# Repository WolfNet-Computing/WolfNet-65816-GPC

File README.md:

# WolfNet-65816-GPC
 WolfNet Computing 65816 based General Purpose Computer

Intended as an upgrade to the WolfNet-65C02-WBC, this computer is more general purpose in design and nature. Text-based USB-Serial control makes connecting to it easy. You don't even need a spare screen or keyboard. Plug it in to your computer, power it on and away you go.

Features:  
 - 65C816 Based design
 - USB Type-B Connnector, MCP2200 and SC28L91 for I/O (Think keyboard, mouse and screen but as a program on your PC, connecting to the device.)
 - ATF1508AS Based Reprogrammable Address Decoder and DMA Controller
 - ATX 20-Pin Power Connector
 - 65-SIB Serial Interface Bus
 - 40-Pin IDE Connector for PATA HDDs
 - 16 MiB Flash ROM
 - 16 MiB SRAM
 - Built-in JTAG-ISP Header for ATF1508AS

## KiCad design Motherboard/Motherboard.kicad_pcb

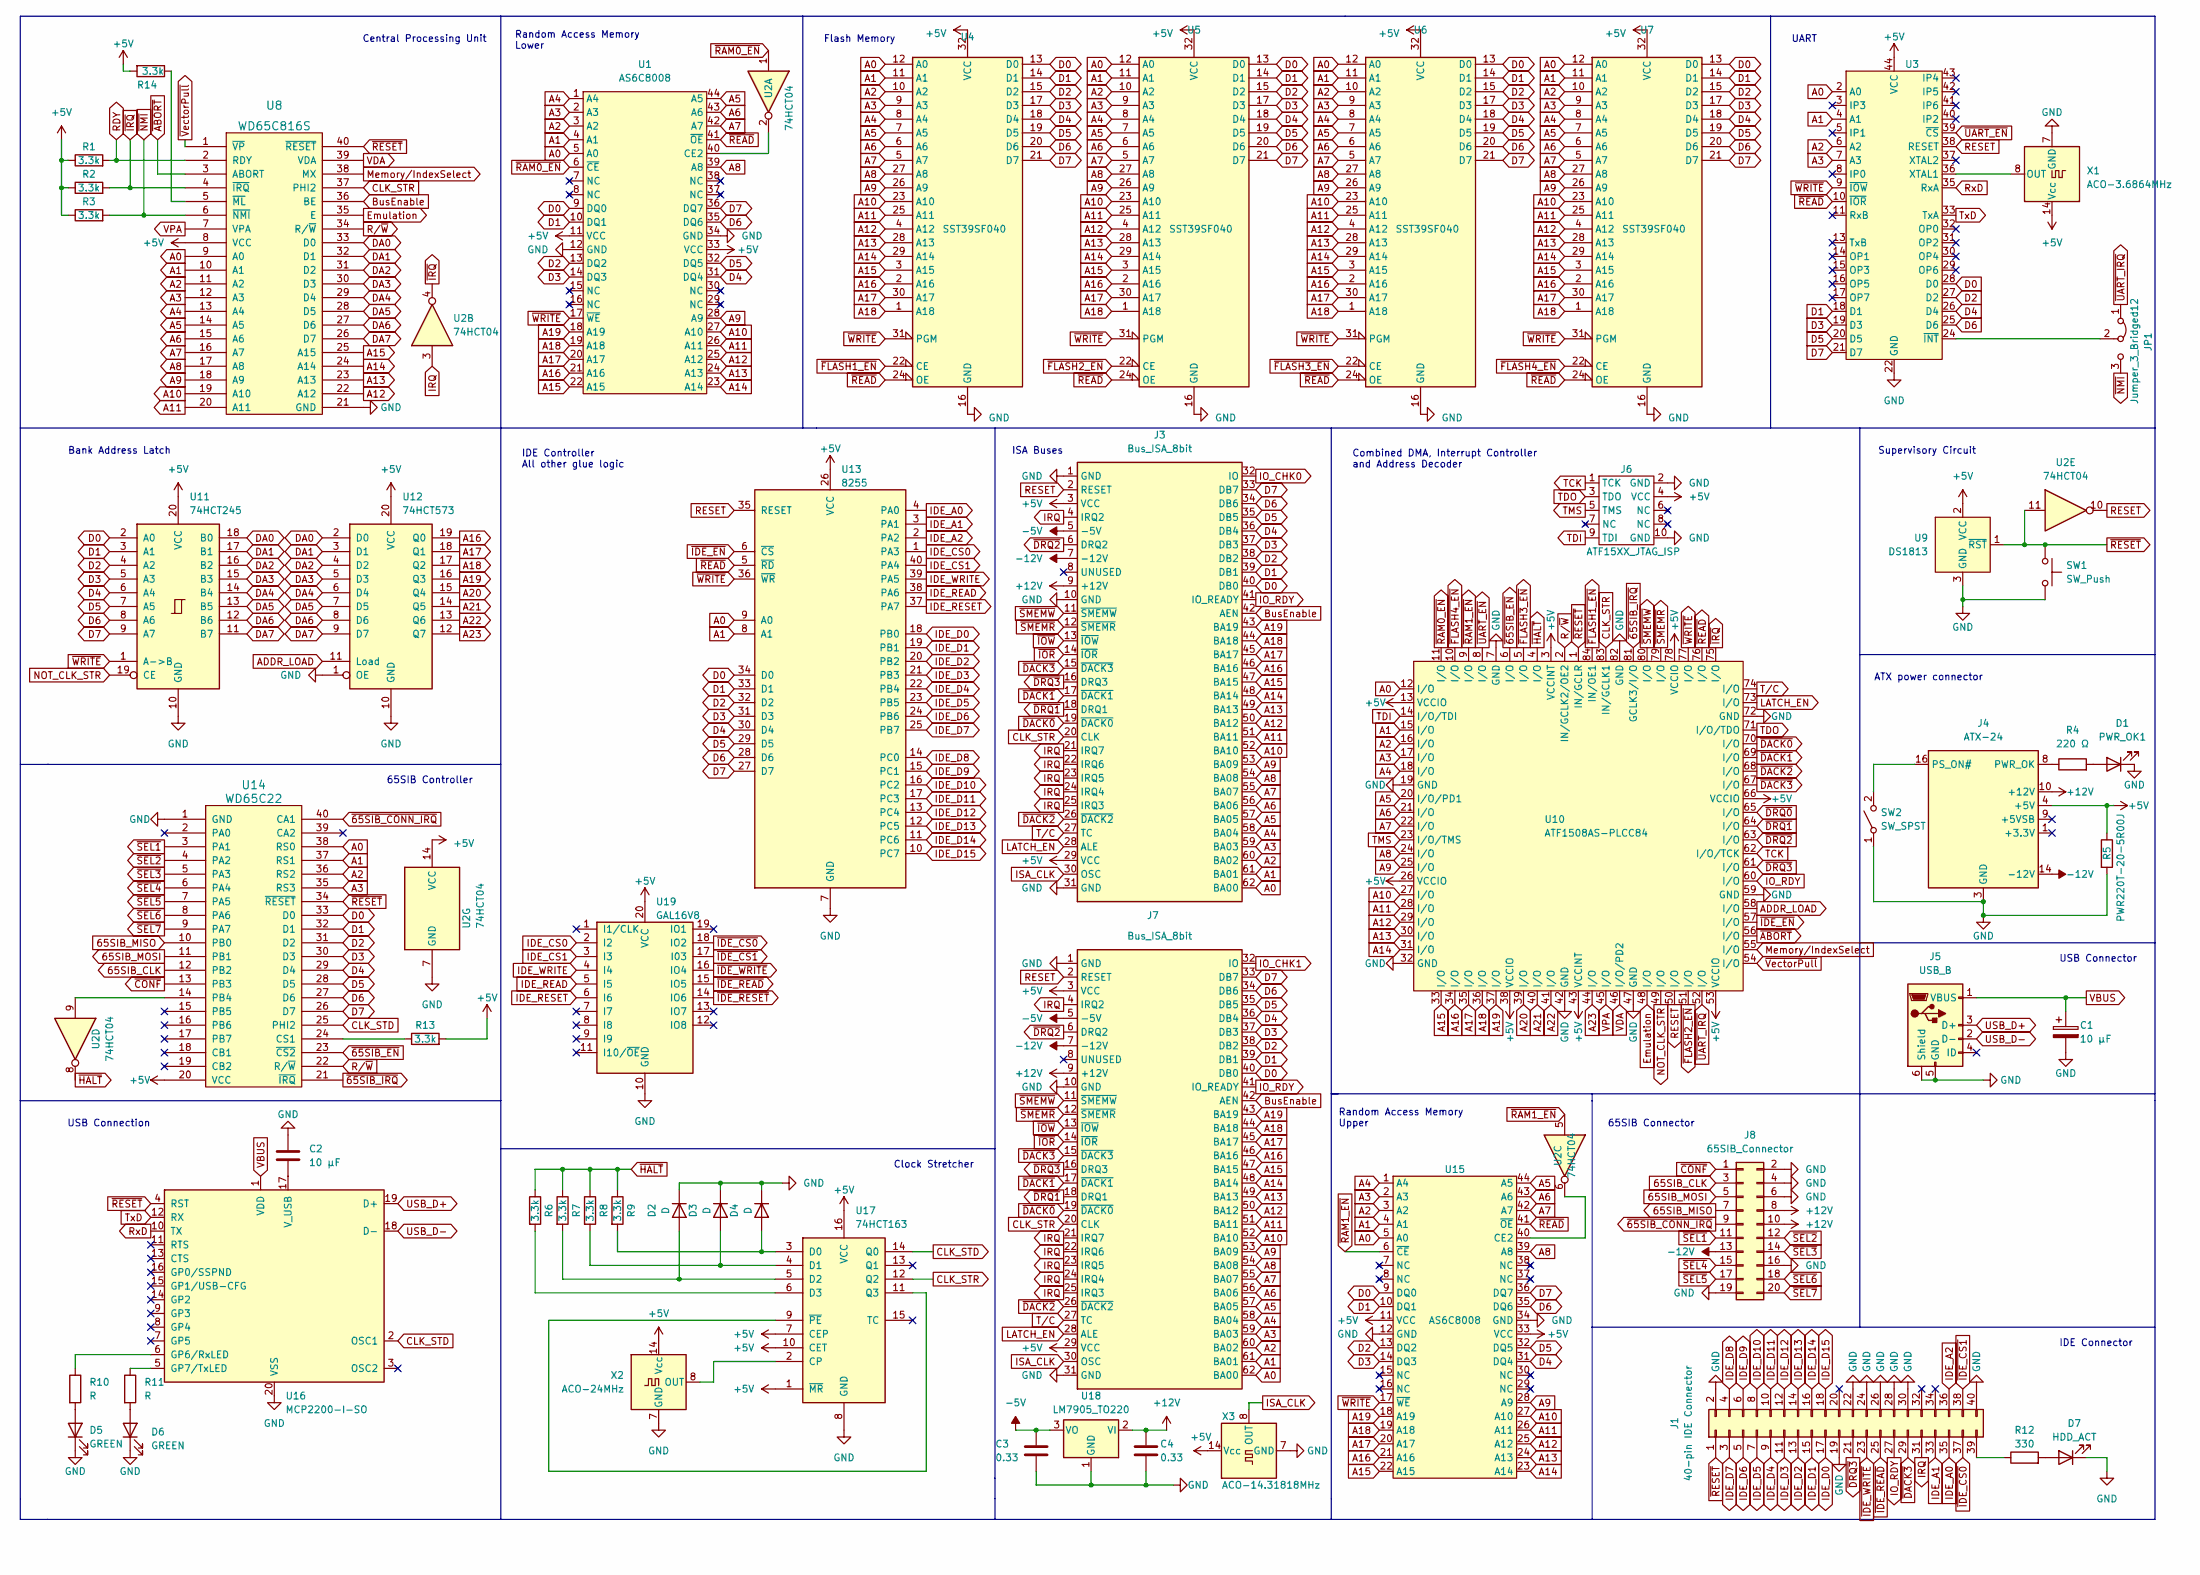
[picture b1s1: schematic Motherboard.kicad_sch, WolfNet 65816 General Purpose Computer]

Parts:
C1, C2: 10 µF; CP_Radial_D5.0mm_P2.50mm
C3, C4: 0.33; C_Disc_D3.8mm_W2.6mm_P2.50mm
D1: PWR_OK1; LED_D3.0mm
D2, D3, D4: D; D_A-405_P7.62mm_Horizontal
D5, D6: GREEN; LED_D3.0mm
D7: HDD_ACT; LED_D5.0mm
J1: 40-pin IDE Connector; PinHeader_2x20_P2.54mm_Vertical
J3, J7: Bus_ISA_8bit; PinSocket_2x31_P1.00mm_Vertical_SMD
J4: ATX-24; Molex_Mini-Fit_Jr_5569-24A2_2x12_P4.20mm_Horizontal
J5: USB_B; USB_Mini-B_Tensility_54-00023_Vertical
J6: ATF15XX_JTAG_ISP; PinHeader_2x05_P2.54mm_Vertical
J8: 65SIB_Connector; PinHeader_2x10_P2.54mm_Vertical
JP1: Jumper_3_Bridged12; PinHeader_1x03_P2.54mm_Vertical
R1, R2, R3, R6, R7, R8, R9, R13, R14: 3.3k; R_Axial_DIN0207_L6.3mm_D2.5mm_P7.62mm_Horizontal
R4: 220 Ω; R_Axial_DIN0207_L6.3mm_D2.5mm_P7.62mm_Horizontal
R5: PWR220T-20-5R00J; TO-220-2_Horizontal_TabDown
R10, R11: R; R_Axial_DIN0207_L6.3mm_D2.5mm_P7.62mm_Horizontal
R12: 330; R_Axial_DIN0207_L6.3mm_D2.5mm_P7.62mm_Horizontal
SW1: SW_Push; SW_PUSH_6mm
SW2: SW_SPST; SW_DIP_SPSTx01_Slide_6.7x4.1mm_W7.62mm_P2.54mm_LowProfile
U1, U15: AS6C8008; TSOP-II-44_10.16x18.41mm_P0.8mm
U2: 74HCT04; DIP-14_W7.62mm_Socket_LongPads
U3: PLCC-44_THT-Socket
U4, U5, U6, U7: SST39SF040; DIP-32_W15.24mm_Socket_LongPads
U8: WD65C816S; DIP-40_W15.24mm_Socket_LongPads
U9: DS1813; TO-92_Inline
U10: ATF1508AS-PLCC84; PLCC-84_THT-Socket
U11: 74HCT245; DIP-20_W7.62mm_Socket_LongPads
U12: 74HCT573; DIP-20_W7.62mm_Socket_LongPads
U13: 8255; DIP-40_W15.24mm
U14: WD65C22; DIP-40_W15.24mm_Socket_LongPads
U16: MCP2200-I-SO; SOIC-20W_7.5x12.8mm_P1.27mm
U17: 74HCT163; DIP-16_W7.62mm_Socket_LongPads
U18: LM7905_TO220; TO-220-3_Vertical
U19: GAL16V8; DIP-20_W7.62mm_Socket_LongPads
X1: ACO-3.6864MHz; Oscillator_DIP-14
X2: ACO-24MHz; Oscillator_DIP-14
X3: ACO-14.31818MHz; Oscillator_DIP-14

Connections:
65SIB_CLK: J8.3 (CLK), U14.12 (PB2)
65SIB_MISO: J8.7 (MISO), U14.10 (PB0)
65SIB_MOSI: J8.5 (MOSI), U14.11 (PB1)
+5V: J3.3 (VCC), J3.29 (VCC), J4.4 (+5V), J4.6 (+5V), J4.21 (+5V), J4.22 (+5V), J4.23 (+5V), J6.4 (VCC), J7.3 (VCC), J7.29 (VCC), R1.1, R2.1, R3.1, R5.1, R13.2, R14.2, U1.11 (VCC), U1.33 (VCC), U2.14 (VCC), U3.44 (VCC), U4.32 (VCC), U5.32 (VCC), U6.32 (VCC), U7.32 (VCC), U8.8 (VCC), U9.2 (VCC), U10.3 (VCCINT), U10.13 (VCCIO), U10.26 (VCCIO), U10.38 (VCCIO), U10.43 (VCCINT), U10.53 (VCCIO), U10.66 (VCCIO), U10.78 (VCCIO), U11.20 (VCC), U12.20 (VCC), U13.26 (VCC), U14.20 (VCC), U15.11 (VCC), U15.33 (VCC), U17.1 (~MR), U17.7 (CEP), U17.10 (CET), U17.16 (VCC), U19.20 (VCC), X1.14 (Vcc), X2.14 (Vcc), X3.14 (Vcc)
+12V: C4.1, J3.9 (+12V), J4.10 (+12V), J4.11 (+12V), J7.9 (+12V), J8.8 (12v), J8.10 (12v), U18.2 (VI)
-5V: C3.1, J3.5 (-5V), J7.5 (-5V), U18.3 (VO)
-12V: J3.7 (-12V), J4.14 (-12V), J7.7 (-12V), J8.13 (-12v)
A0: J3.62 (BA00), J7.62 (BA00), U1.5 (A0), U3.2 (A0), U4.12 (A0), U5.12 (A0), U6.12 (A0), U7.12 (A0), U8.9 (A0), U10.12 (I/O), U13.9 (A0), U14.38 (RS0), U15.5 (A0)
A1: J3.61 (BA01), J7.61 (BA01), U1.4 (A1), U3.4 (A1), U4.11 (A1), U5.11 (A1), U6.11 (A1), U7.11 (A1), U8.10 (A1), U10.15 (I/O), U13.8 (A1), U14.37 (RS1), U15.4 (A1)
A2: J3.60 (BA02), J7.60 (BA02), U1.3 (A2), U3.6 (A2), U4.10 (A2), U5.10 (A2), U6.10 (A2), U7.10 (A2), U8.11 (A2), U10.16 (I/O), U14.36 (RS2), U15.3 (A2)
A3: J3.59 (BA03), J7.59 (BA03), U1.2 (A3), U3.7 (A3), U4.9 (A3), U5.9 (A3), U6.9 (A3), U7.9 (A3), U8.12 (A3), U10.17 (I/O), U14.35 (RS3), U15.2 (A3)
A4: J3.58 (BA04), J7.58 (BA04), U1.1 (A4), U4.8 (A4), U5.8 (A4), U6.8 (A4), U7.8 (A4), U8.13 (A4), U10.18 (I/O), U15.1 (A4)
A5: J3.57 (BA05), J7.57 (BA05), U1.44 (A5), U4.7 (A5), U5.7 (A5), U6.7 (A5), U7.7 (A5), U8.14 (A5), U10.20 (I/O/PD1), U15.44 (A5)
A6: J3.56 (BA06), J7.56 (BA06), U1.43 (A6), U4.6 (A6), U5.6 (A6), U6.6 (A6), U7.6 (A6), U8.15 (A6), U10.21 (I/O), U15.43 (A6)
A7: J3.55 (BA07), J7.55 (BA07), U1.42 (A7), U4.5 (A7), U5.5 (A7), U6.5 (A7), U7.5 (A7), U8.16 (A7), U10.22 (I/O), U15.42 (A7)
A8: J3.54 (BA08), J7.54 (BA08), U1.39 (A8), U4.27 (A8), U5.27 (A8), U6.27 (A8), U7.27 (A8), U8.17 (A8), U10.24 (I/O), U15.39 (A8)
A9: J3.53 (BA09), J7.53 (BA09), U1.28 (A9), U4.26 (A9), U5.26 (A9), U6.26 (A9), U7.26 (A9), U8.18 (A9), U10.25 (I/O), U15.28 (A9)
A10: J3.52 (BA10), J7.52 (BA10), U1.27 (A10), U4.23 (A10), U5.23 (A10), U6.23 (A10), U7.23 (A10), U8.19 (A10), U10.27 (I/O), U15.27 (A10)
A11: J3.51 (BA11), J7.51 (BA11), U1.26 (A11), U4.25 (A11), U5.25 (A11), U6.25 (A11), U7.25 (A11), U8.20 (A11), U10.28 (I/O), U15.26 (A11)
A12: J3.50 (BA12), J7.50 (BA12), U1.25 (A12), U4.4 (A12), U5.4 (A12), U6.4 (A12), U7.4 (A12), U8.22 (A12), U10.29 (I/O), U15.25 (A12)
A13: J3.49 (BA13), J7.49 (BA13), U1.24 (A13), U4.28 (A13), U5.28 (A13), U6.28 (A13), U7.28 (A13), U8.23 (A13), U10.30 (I/O), U15.24 (A13)
A14: J3.48 (BA14), J7.48 (BA14), U1.23 (A14), U4.29 (A14), U5.29 (A14), U6.29 (A14), U7.29 (A14), U8.24 (A14), U10.31 (I/O), U15.23 (A14)
A15: J3.47 (BA15), J7.47 (BA15), U1.22 (A15), U4.3 (A15), U5.3 (A15), U6.3 (A15), U7.3 (A15), U8.25 (A15), U10.33 (I/O), U15.22 (A15)
A16: J3.46 (BA16), J7.46 (BA16), U1.21 (A16), U4.2 (A16), U5.2 (A16), U6.2 (A16), U7.2 (A16), U10.34 (I/O), U12.19 (Q0), U15.21 (A16)
A17: J3.45 (BA17), J7.45 (BA17), U1.20 (A17), U4.30 (A17), U5.30 (A17), U6.30 (A17), U7.30 (A17), U10.35 (I/O), U12.18 (Q1), U15.20 (A17)
A18: J3.44 (BA18), J7.44 (BA18), U1.19 (A18), U4.1 (A18), U5.1 (A18), U6.1 (A18), U7.1 (A18), U10.36 (I/O), U12.17 (Q2), U15.19 (A18)
A19: J3.43 (BA19), J7.43 (BA19), U1.18 (A19), U10.37 (I/O), U12.16 (Q3), U15.18 (A19)
A20: U10.39 (I/O), U12.15 (Q4)
A21: U10.40 (I/O), U12.14 (Q5)
A22: U10.41 (I/O), U12.13 (Q6)
A23: U10.44 (I/O), U12.12 (Q7)
ADDR_LOAD: U10.58 (I/O), U12.11 (Load)
BusEnable: J3.42 (AEN), J7.42 (AEN), U8.36 (BE)
CLK_STD: U14.25 (PHI2), U16.2 (OSC1), U17.14 (Q0)
CLK_STR: J3.20 (CLK), J7.20 (CLK), U8.37 (PHI2), U10.83 (IN/GCLK1), U17.12 (Q2)
D0: J3.40 (DB0), J7.40 (DB0), U1.9 (DQ0), U3.28 (D0), U4.13 (D0), U5.13 (D0), U6.13 (D0), U7.13 (D0), U11.2 (A0), U13.34 (D0), U14.33 (D0), U15.9 (DQ0)
D1: J3.39 (DB1), J7.39 (DB1), U1.10 (DQ1), U3.18 (D1), U4.14 (D1), U5.14 (D1), U6.14 (D1), U7.14 (D1), U11.3 (A1), U13.33 (D1), U14.32 (D1), U15.10 (DQ1)
D2: J3.38 (DB2), J7.38 (DB2), U1.13 (DQ2), U3.27 (D2), U4.15 (D2), U5.15 (D2), U6.15 (D2), U7.15 (D2), U11.4 (A2), U13.32 (D2), U14.31 (D2), U15.13 (DQ2)
D3: J3.37 (DB3), J7.37 (DB3), U1.14 (DQ3), U3.19 (D3), U4.17 (D3), U5.17 (D3), U6.17 (D3), U7.17 (D3), U11.5 (A3), U13.31 (D3), U14.30 (D3), U15.14 (DQ3)
D4: J3.36 (DB4), J7.36 (DB4), U1.31 (DQ4), U3.26 (D4), U4.18 (D4), U5.18 (D4), U6.18 (D4), U7.18 (D4), U11.6 (A4), U13.30 (D4), U14.29 (D4), U15.31 (DQ4)
D5: J3.35 (DB5), J7.35 (DB5), U1.32 (DQ5), U3.20 (D5), U4.19 (D5), U5.19 (D5), U6.19 (D5), U7.19 (D5), U11.7 (A5), U13.29 (D5), U14.28 (D5), U15.32 (DQ5)
D6: J3.34 (DB6), J7.34 (DB6), U1.35 (DQ6), U3.25 (D6), U4.20 (D6), U5.20 (D6), U6.20 (D6), U7.20 (D6), U11.8 (A6), U13.28 (D6), U14.27 (D6), U15.35 (DQ6)
D7: J3.33 (DB7), J7.33 (DB7), U1.36 (DQ7), U3.21 (D7), U4.21 (D7), U5.21 (D7), U6.21 (D7), U7.21 (D7), U11.9 (A7), U13.27 (D7), U14.26 (D7), U15.36 (DQ7)
DA0: U8.33 (D0), U11.18 (B0), U12.2 (D0)
DA1: U8.32 (D1), U11.17 (B1), U12.3 (D1)
DA2: U8.31 (D2), U11.16 (B2), U12.4 (D2)
DA3: U8.30 (D3), U11.15 (B3), U12.5 (D3)
DA4: U8.29 (D4), U11.14 (B4), U12.6 (D4)
DA5: U8.28 (D5), U11.13 (B5), U12.7 (D5)
DA6: U8.27 (D6), U11.12 (B6), U12.8 (D6)
DA7: U8.26 (D7), U11.11 (B7), U12.9 (D7)
Emulation: U8.35 (E), U10.48 (I/O)
GND: C1.2, C2.1, C3.2, C4.2, D1.1 (K), D2.1 (K), D3.1 (K), D4.1 (K), D5.1 (K), D6.1 (K), D7.1 (K), J1.2, J1.19, J1.22, J1.24, J1.26, J1.28, J1.30, J1.40, J3.1 (GND), J3.10 (GND), J3.31 (GND), J4.3 (GND), J4.5 (GND), J4.7 (GND), J4.15 (GND), J4.17 (GND), J4.18 (GND), J4.19 (GND), J4.24 (GND), J5.5 (GND), J5.6 (Shield), J6.2 (GND), J6.10 (GND), J7.1 (GND), J7.10 (GND), J7.31 (GND), J8.2 (GND), J8.4 (GND), J8.6 (eGND), J8.16 (GND), J8.19 (GND), R5.2, SW1.2, SW2.1 (A), U1.12 (GND), U1.34 (GND), U2.7 (GND), U3.22 (GND), U4.16 (GND), U5.16 (GND), U6.16 (GND), U7.16 (GND), U8.21 (GND), U9.3 (GND), U10.7 (GND), U10.19 (GND), U10.32 (GND), U10.42 (GND), U10.47 (GND), U10.59 (GND), U10.72 (GND), U10.82 (GND), U11.10 (GND), U12.1 (OE), U12.10 (GND), U13.7 (GND), U14.1 (GND), U15.12 (GND), U15.34 (GND), U16.20 (VSS), U17.8 (GND), U18.1 (GND), U19.10 (GND), X1.7 (GND), X2.7 (GND), X3.7 (GND)
IDE_A0: J1.35, U13.4 (PA0)
IDE_A1: J1.33, U13.3 (PA1)
IDE_A2: J1.36, U13.2 (PA2)
IDE_CS0: U13.1 (PA3), U19.2 (I2)
IDE_CS1: U13.40 (PA4), U19.3 (I3)
IDE_D0: J1.17, U13.18 (PB0)
IDE_D1: J1.15, U13.19 (PB1)
IDE_D2: J1.13, U13.20 (PB2)
IDE_D3: J1.11, U13.21 (PB3)
IDE_D4: J1.9, U13.22 (PB4)
IDE_D5: J1.7, U13.23 (PB5)
IDE_D6: J1.5, U13.24 (PB6)
IDE_D7: J1.3, U13.25 (PB7)
IDE_D8: J1.4, U13.14 (PC0)
IDE_D9: J1.6, U13.15 (PC1)
IDE_D10: J1.8, U13.16 (PC2)
IDE_D11: J1.10, U13.17 (PC3)
IDE_D12: J1.12, U13.13 (PC4)
IDE_D13: J1.14, U13.12 (PC5)
IDE_D14: J1.16, U13.11 (PC6)
IDE_D15: J1.18, U13.10 (PC7)
IDE_READ: U13.38 (PA6), U19.5 (I5)
IDE_RESET: U13.37 (PA7), U19.6 (I6)
IDE_WRITE: U13.39 (PA5), U19.4 (I4)
IO_CHK0: J3.32 (IO)
IO_CHK1: J7.32 (IO)
IO_RDY: J1.27, J3.41 (IO_READY), J7.41 (IO_READY), U10.60 (I/O)
IRQ: J1.31, J3.4 (IRQ2), J3.21 (IRQ7), J3.22 (IRQ6), J3.23 (IRQ5), J3.24 (IRQ4), J3.25 (IRQ3), J7.4 (IRQ2), J7.21 (IRQ7), J7.22 (IRQ6), J7.23 (IRQ5), J7.24 (IRQ4), J7.25 (IRQ3), U2.3
ISA_CLK: J3.30 (OSC), J7.30 (OSC), X3.8 (OUT)
LATCH_EN: J3.28 (ALE), J7.28 (ALE), U10.73 (I/O)
Memory/IndexSelect: U8.38 (MX), U10.55 (I/O)
NOT_CLK_STR: U10.49 (I/O), U11.19 (CE)
unnamed: D1.2 (A), R4.2
unnamed: D2.2 (A), R7.2, U17.5 (D2)
unnamed: D3.2 (A), R8.2, U17.4 (D1)
unnamed: D4.2 (A), R9.2, U17.3 (D0)
unnamed: D5.2 (A), R10.2
unnamed: D6.2 (A), R11.2
unnamed: D7.2 (A), R12.2
unnamed: J1.39, R12.1
unnamed: J4.16 (PS_ON#), SW2.2 (B)
unnamed: J4.8 (PWR_OK), R4.1
unnamed: JP1.2 (C), U3.24 (~INT)
unnamed: U1.40 (CE2), U2.2
unnamed: U3.36 (XTAL1), X1.8 (OUT)
unnamed: R14.1, U8.5 (~ML)
unnamed: R13.1, U14.24 (CS1)
unnamed: U2.9, U14.14 (PB4)
unnamed: U2.6, U15.40 (CE2)
unnamed: R10.1, U16.6 (GP6/RxLED)
unnamed: R11.1, U16.5 (GP7/TxLED)
unnamed: C2.2, U16.17 (V_USB)
unnamed: U17.2 (CP), X2.8 (OUT)
unnamed: R6.2, U17.6 (D3)
unnamed: U17.9 (~PE), U17.11 (Q3)
RDY: R1.2, U8.2 (RDY)
RESET: J3.2 (RESET), J7.2 (RESET), U2.10, U3.38 (RESET), U10.50 (I/O), U13.35 (RESET)
RxD: U3.35 (RxA), U16.10 (TX)
R/~W: U8.34 (R/~W), U10.2 (IN/GCLK2/OE2), U14.22 (R/~W)
TCK: J6.1 (TCK), U10.62 (I/O/TCK)
TDI: J6.9 (TDI), U10.14 (I/O/TDI)
TDO: J6.3 (TDO), U10.71 (I/O/TDO)
TMS: J6.5 (TMS), U10.23 (I/O/TMS)
TxD: U3.33 (TxA), U16.12 (RX)
T/C: J3.27 (TC), J7.27 (TC), U10.74 (I/O)
USB_D+: J5.3 (D+), U16.19 (D+)
USB_D-: J5.2 (D-), U16.18 (D-)
VBUS: C1.1, J5.1 (VBUS), U16.1 (VDD)
VDA: U8.39 (VDA), U10.46 (I/O/PD2)
VPA: U8.7 (VPA), U10.45 (I/O)
~65SIB_CONN_IRQ: J8.9 (IRO\), U14.40 (CA1)
~65SIB_EN: U10.6 (I/O), U14.23 (~CS2)
~65SIB_IRQ: U10.81 (GCLK3/I/O), U14.21 (~IRQ)
~ABORT: U8.3 (ABORT), U10.56 (I/O)
~CONF: J8.1 (CONF\), U14.13 (PB3)
~DACK0: J3.19 (~DACK0), J7.19 (~DACK0), U10.70 (I/O)
~DACK1: J3.17 (~DACK1), J7.17 (~DACK1), U10.69 (I/O)
~DACK2: J3.26 (~DACK2), J7.26 (~DACK2), U10.68 (I/O)
~DACK3: J1.29, J3.15 (~DACK3), J7.15 (~DACK3), U10.67 (I/O)
~DRQ0: U10.65 (I/O)
~DRQ1: J3.18 (DRQ1), J7.18 (DRQ1), U10.64 (I/O)
~DRQ2: J3.6 (DRQ2), J7.6 (DRQ2), U10.63 (I/O)
~DRQ3: J1.21, J3.16 (DRQ3), J7.16 (DRQ3), U10.61 (I/O)
~FLASH1_EN: U4.22 (CE), U10.84 (IN/OE1)
~FLASH2_EN: U5.22 (CE), U10.51 (I/O)
~FLASH3_EN: U6.22 (CE), U10.5 (I/O)
~FLASH4_EN: U7.22 (CE), U10.10 (I/O)
~HALT: R6.1, R7.1, R8.1, R9.1, U2.8, U10.4 (I/O)
~IDE_CS0: J1.37, U19.18 (IO2)
~IDE_CS1: J1.38, U19.17 (I03)
~IDE_EN: U10.57 (I/O), U13.6 (~CS)
~IDE_READ: J1.25, U19.15 (IO5)
~IDE_RESET: U19.14 (IO6)
~IDE_WRITE: J1.23, U19.16 (IO4)
~IOR: J3.14 (~IOR), J7.14 (~IOR)
~IOW: J3.13 (~IOW), J7.13 (~IOW)
~IRQ: R2.2, U2.4, U8.4 (~IRQ), U10.75 (I/O)
~NMI: JP1.3 (B), R3.2, U8.6 (~NMI)
~RAM0_EN: U1.6 (~CE), U2.1, U10.11 (I/O)
~RAM1_EN: U2.5, U10.9 (I/O), U15.6 (~CE)
~READ: U1.41 (~OE), U3.10 (~IOR), U4.24 (OE), U5.24 (OE), U6.24 (OE), U7.24 (OE), U10.76 (I/O), U13.5 (~RD), U15.41 (~OE)
~RESET: J1.1, SW1.1, U2.11, U8.40 (~RESET), U9.1 (~RST), U10.1 (IN/GCLR), U14.34 (~RESET), U16.4 (RST)
~SEL1: J8.11 (SEL1\), U14.3 (PA1)
~SEL2: J8.12 (SEL2\), U14.4 (PA2)
~SEL3: J8.14 (SEL3\), U14.5 (PA3)
~SEL4: J8.15 (SEL4\), U14.6 (PA4)
~SEL5: J8.17 (SEL5\), U14.7 (PA5)
~SEL6: J8.18 (SEL6\), U14.8 (PA6)
~SEL7: J8.20 (SEL7\), U14.9 (PA7)
~SMEMR: J3.12 (~SMEMR), J7.12 (~SMEMR), U10.79 (I/O)
~SMEMW: J3.11 (~SMEMW), J7.11 (~SMEMW), U10.80 (I/O)
~UART_EN: U3.39 (~CS), U10.8 (I/O)
~UART_IRQ: JP1.1 (A), U10.52 (I/O)
~VectorPull: U8.1 (~VP), U10.54 (I/O)
~WRITE: U1.17 (~WE), U3.9 (~IOW), U4.31 (PGM), U5.31 (PGM), U6.31 (PGM), U7.31 (PGM), U10.77 (I/O), U11.1 (A->B), U13.36 (~WR), U15.17 (~WE)

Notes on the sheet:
IDE Controller All other glue logic
Flash Memory
ISA Buses
USB Connector
Central Processing Unit
ATX power connector
IDE Connector
Supervisory Circuit
Combined DMA, Interrupt Controller and Address Decoder
65SIB Controller
Clock Stretcher
UART
USB Connection
Random Access Memory Lower
Random Access Memory Upper
Bank Address Latch
65SIB Connector

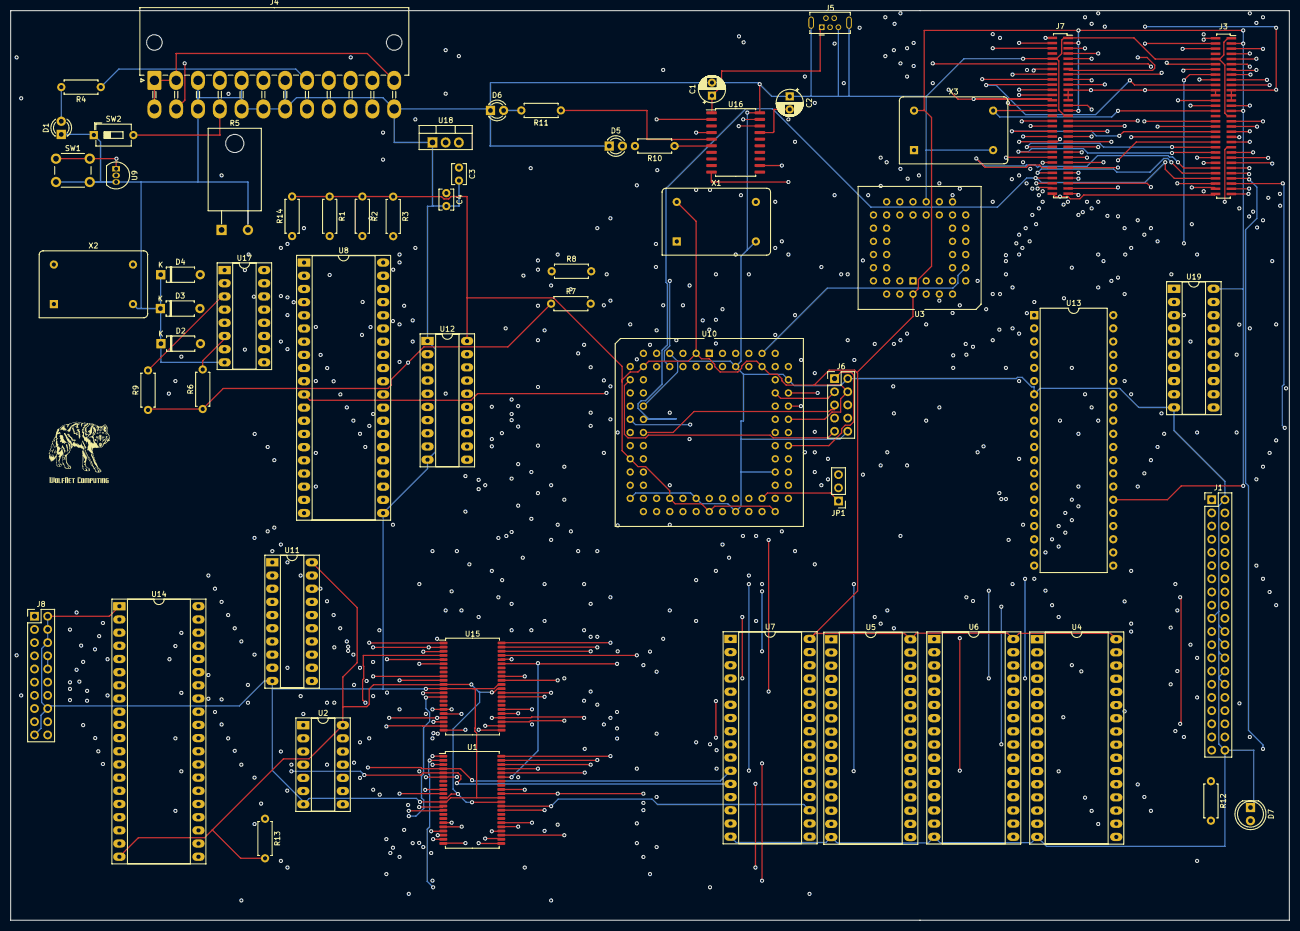
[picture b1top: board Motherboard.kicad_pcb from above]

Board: 4 copper layers, 246.4 x 175.3 mm, 57 parts (0 on the bottom side), 164 nets.

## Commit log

2022-10-21 Repository setup...
2022-10-21 First upload from Git...
2022-10-21 Added and connected CPU...
2022-10-21 Added and connected RAM...
2022-10-22 Added and connected 2 ROM Banks...
2022-10-24 Almost there...
2022-10-25 Changing ROM to Flash memory...
2022-10-25 Added licensing and security information...
2022-10-26 Replaced ROM with Flash memory...
2022-10-27 Create WolfNet-65816-GPC.kicad_sch-bak
2022-10-29 Connected ISA ports...
2022-10-29 Migrated files to Motherboard subfolder...
2022-10-30 Create #auto_saved_files#
2022-10-30 Finished schematic for address decoding...
2022-11-01 Added Address Decoder and DMAC firmware...
2022-11-03 Updated firmware...
2023-03-20 Started on PCB layout...
2023-03-21 More on the road to 2.0
2023-03-26 On the road to 1.0...
2023-03-30 Motherboard PCB updated...
2023-04-18 Added traces...
2023-04-20 Added IDE controller and fixed HALT signal...
2023-04-21 Update IDE Interface, controller and added parts to PCB...
2023-04-21 477 unrouted traces...
2023-04-21 475 unrouted traces...
2023-04-21 472 unrouted traces...
2023-04-21 443 unrouted traces...
2023-04-21 354 unrouted traces...
2023-04-22 350 unrouted traces...
2023-04-22 Fixed clock connections...
2023-04-22 340 unrouted traces...
2023-04-22 334 unrouted traces...
2023-04-24 Replaced discontinued DUART and fixed wiring...
2023-04-24 Updated component footprints...
2023-04-24 343 unrouted traces...
2023-04-24 Fixed D7 line...
2023-04-24 337 unrouted traces...
2023-04-24 332 unrouted traces...
2023-04-24 325 unrouted traces...
2023-04-24 316 unrouted traces...
2023-04-27 307 unrouted traces...
2023-04-28 305 unrouted traces...
2023-04-28 300 unrouted traces...
2023-04-28 288 unrouted traces...
2023-04-28 268 unrouted traces...
2023-04-28 265 unrouted traces...
2023-04-29 260 unrouted traces...
2023-04-29 230 unrouted traces...
2023-04-29 226 unrouted traces...
2023-04-29 222 unrouted traces...
2023-04-29 200 unrouted traces...
2023-04-29 190 unrouted traces...
2023-04-29 180 unrouted traces...
2023-04-29 176 unrouted traces...
2023-04-29 173 unrouted traces...
2023-04-29 150 Unrouted traces...
2023-04-29 134 Unrouted traces...
2023-04-29 118 Unrouted traces...
2023-04-29 110 Unrouted traces...
2023-04-29 103 Unrouted traces...
2023-04-30 98 Unrouted traces...
2023-04-30 92 Unrouted traces...
2023-04-30 Fixed DRQ1 line...
2023-04-30 86 Unrouted traces...
2023-04-30 80 Unrouted traces...
2023-04-30 72 Unrouted traces...
2023-04-30 69 Unrouted traces...
2023-04-30 64 Unrouted traces...
2023-04-30 54 Unrouted traces...
2023-04-30 36 Unrouted traces...
2023-04-30 10 Unrouted traces...
2023-04-30 Routing Complete...

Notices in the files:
Motherboard/Motherboard.kicad_pcb:
Released under the Solderpad Hardware License 2.1
